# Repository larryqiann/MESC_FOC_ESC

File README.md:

# MESC_FOC_ESC
MESC, Molony ESC, STM32F303 based FOC+BLDC ready, HALL, Encoder, Sensorless, single sides, 2 layer, ~90A @48V

This ESC is intended as a cost optimised alternative to the VESC, by utilising:

Standalone, industry standard footprint gate drivers

Standard D2PAK or H2PAK FETs

Cheap (~2.5$) STM32F303CB microcontroller

Board dimensions 100mmx50mm, so that it can be panelised and manufactured by JLCPCB, or two boards can be combined into one 100mm2 JLCPCB

It is not cross compatible with VESC software, and does not intend to be. VESC has run away with itself in terms of cost, firmware abstraction... in the opinion of this project's author.

# Current Status:  

## Changes made by larryqiann:
Change power architecture to use MP9486A to create 12V rail, from  which 3.3V and 5V will be regulated to reduce quiescent power draw

Add CAN bus transceiver to support CAN bus integration because F303CB supports CAN2.0b

## Previous:

First build has been made. All functions... function.
Photos in folder! Video of prelim run to be added to Youtube.
Step down works
Step up for Gate drives works
Chip works, all inputs and outputs works
Some concerns about stability of internal opamps... Returning 1.5V instead of 1.6V. First chip soldered returned 1V, and fluctuated by +0.3/-0.1V. 
Motor spins in BLDC mode (6 step) with hall sensors, on Propdrive 2826 1200kV and with APS8072 50kV. Current run up to 20A phase, with minimal PCB heating with no heatsink. Only run to 23V so far, owing to PSU limitation.
FET switching time rather slow with 5 ohm resistors, limiting peak current to 2A (not counting FET and Gate drive resistance) will reduce to 2R7.

# Layout:  
Layout optimised to minimise current loop path, and keep the board completely single sided assembly.

For thermal management, the FETs have vias underneath the drains, which can be interfaced with a heatsink on the PCB underside, using silicone pad/thermal paste & insulator.

# MCU uses:
Timer1 on PA8,9,10 (high) and PB13,14,15 for PWM generation.

Onboard opamps for current sensing and paralelled comparators input on pins PA1,7, PB0.

Phase voltages can be measured on PA3,4,5, or alternatively, digitally read to detect ZC .

Main voltage can be read on PA0.

# Interfaces:
External Interfaces include Hall/Encoder, I2C, PWM in, UART, USB FS.

Hall sensors on Timer4 PB6,7,8, alternatively Encoder can be run on Tim4 PB6,7

Timer3 channel 1 for standard RC PWM input.

USART3 Tx Rx on PB10,11.
USB on PA11,12, with 1k5 pullup to signal FS mode. Canbe used for reflashing (hypothetically).

I2C1 on PA15(SCL) and PB9(SDA), with a plug for a standard SSD1306 breakout. Alternatively, inertial sensor board could be plugged on breakout wire.

Expected BoM cost:  
0.4USD board  
6x2USD FETs  
2.5USD MCU  
3x1USD gate drives  
1USD SMPS converter  
0.4USD inductor  
??? connector cost (dependent on what's fitted, wire in...)  
0.3USD linear reg  
~3USD caps (dependent on how many you want to solder on, which is dependent on distance to battery, desire to comply with EMC, headroom above FET voltage... etc.)  
0.6USD shunts and other resistors  
0.3USD Optional TVS diode, primarily to protect SMPS, which is only rated to 65V  
Total: ~23-24USD

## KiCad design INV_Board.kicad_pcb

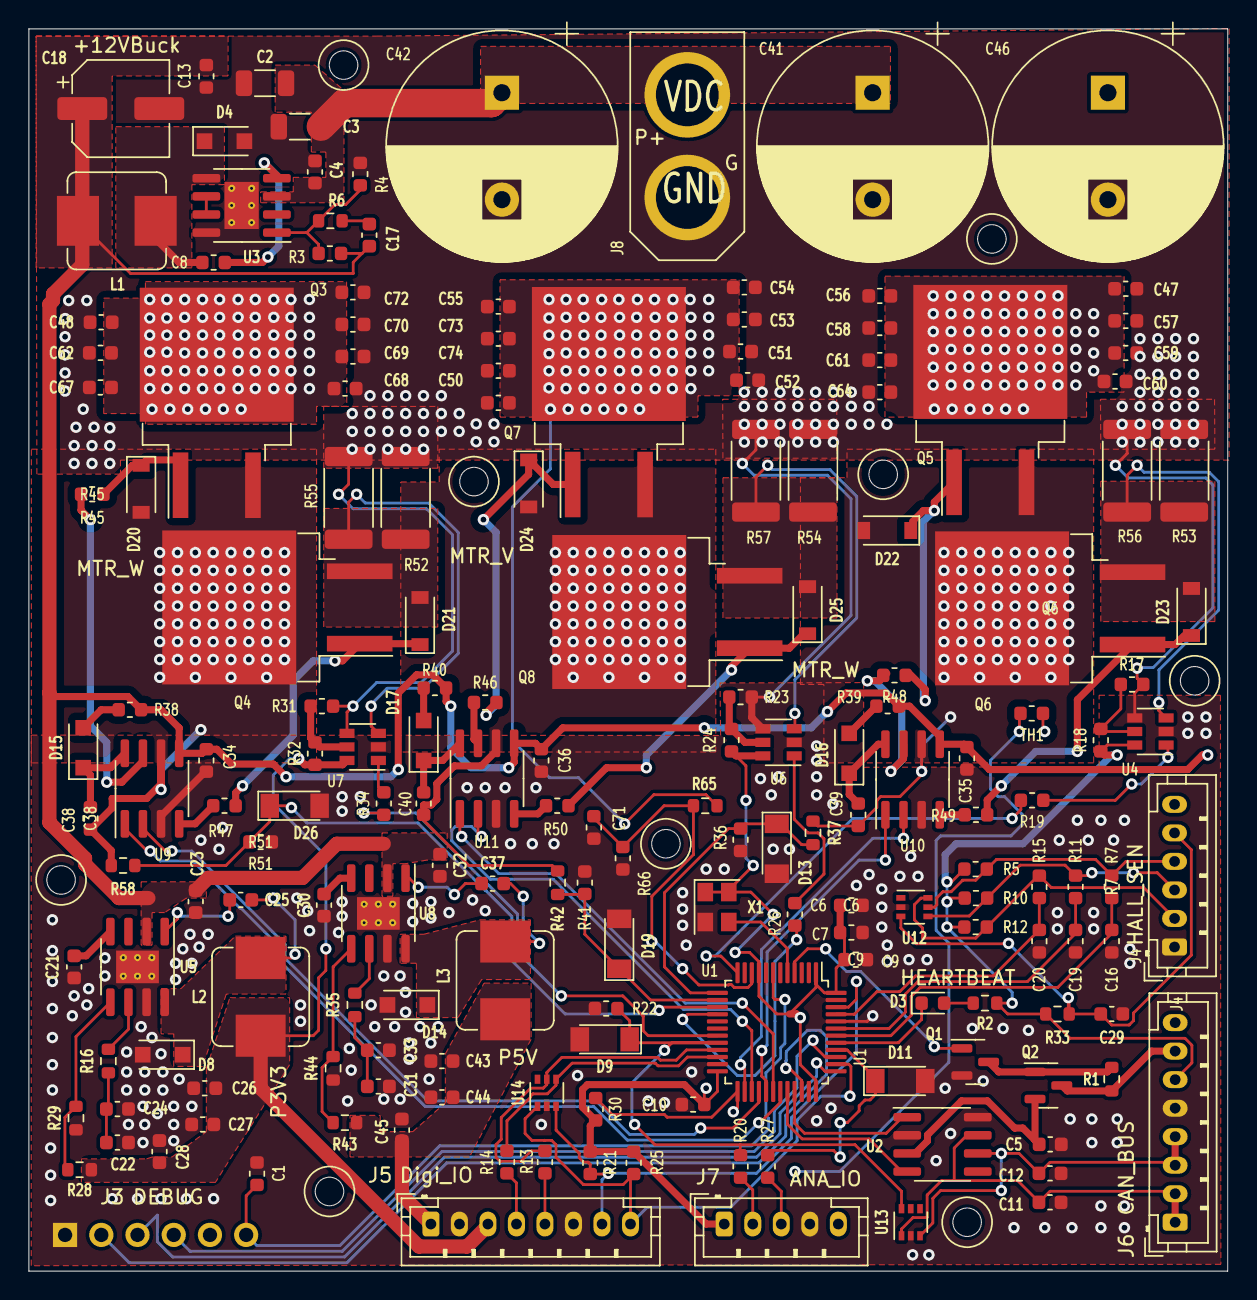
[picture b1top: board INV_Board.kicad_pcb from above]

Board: 4 copper layers, 84.1 x 87.1 mm, 177 parts (1 on the bottom side), 97 nets.

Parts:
C1, C4, C7, C9, C10, C17, C52, C68, C71: C_0.1uF_100V; C_0603_1608Metric
C2, C3: C_2.2uF 100V; C_1206_3216Metric
C5, C8, C25, C37: C_100nF_16V; C_0603_1608Metric
C6, C34, C35, C36, C38, C39, C40, C47, C48, C50, C51, C53, C54, C55, C56, C57, C58, C59, C60, C61, C62, C64, C67, C69, C70, C72, C73, C74: C_1uF_100V; C_0603_1608Metric
C11, C12: C_4.7nF; C_0603_1608Metric
C13, C23, C26, C27, C28, C32, C43, C44, C45: C_10uF_25V; C_0603_1608Metric
C16, C19, C20, C29: C_100pF_16V; C_0603_1608Metric
C18: C_100uF_25V; CP_Elec_6.3x7.7
C21, C30: C_8.2nF; C_0603_1608Metric
C22, C31: C_10pF; C_0603_1608Metric
C24, C33: C_5.1nF; C_0603_1608Metric
C41, C42, C46: CP_470uF+; CP_Radial_D16.0mm_P7.50mm
D3: LED_Small; LED_0603_1608Metric
D4, D8, D14, D15, D16, D17: D_Sch_100V_2A; D_SOD-123F
D9, D11, D13: D_Zener_3v3; D_MiniMELF
D19, D26: D_Zener_3V3; D_MiniMELF
D20, D21, D22, D23, D24, D25: D_Zener_16V; D_SOD-123
J3: Conn_01x06_Male; PinHeader_1x06_P2.54mm_Vertical
J4: Conn_01x06_Female; JST_PH_B6B-PH-K_1x06_P2.00mm_Vertical
J5, J6: Conn_01x08_Female; JST_PH_B8B-PH-K_1x08_P2.00mm_Vertical
J7: Conn_01x05_Male; JST_PH_B5B-PH-K_1x05_P2.00mm_Vertical
J8: Conn_01x02_Male; XT60
L1: L_47uH_2.0A; L_Bourns_SRP7028A_7.3x6.6mm
L2, L3: L_15uH_3A; L_Bourns_SRP7028A_7.3x6.6mm
Q1: 2N7002; SOT-23
Q2: AO3401A; SOT-23
Q3, Q4, Q5, Q6, Q7, Q8: CRSS037N10N; TO-263-2
R1, R37, R42, R58, R65: R_82k; R_0603_1608Metric
R2, R4, R6, R7, R11, R15, R30, R33: R_4k7; R_0603_1608Metric
R3: R_590K; R_0603_1608Metric
R5, R10, R12, R20, R21, R22, R25, R27, R36, R41, R51, R66: R_1.5k; R_0603_1608Metric
R13, R14: R_100; R_0603_1608Metric
R16, R35: R_5.76K; R_0603_1608Metric
R17, R18, R23, R24, R31, R32: R_30K; R_0603_1608Metric
R19, R26, R34: R_150; R_0603_1608Metric
R28, R43: R_10.2K; R_0603_1608Metric
R29: R_3.24K; R_0603_1608Metric
R38, R39, R40, R45, R46, R47, R48, R49, R50: R_5; R_0603_1608Metric
R44: R_1.96K; R_0603_1608Metric
R52, R53, R54, R55, R56, R57: Shunt; R_2512_6332Metric
TH1: Thermistor_NTC; R_0603_1608Metric
U1: STM32F303CBTx; LQFP-48_7x7mm_P0.5mm
U2: TJA1051T; SOIC-8_3.9x4.9mm_P1.27mm
U3: MP9486A; SOIC-8-1EP_3.9x4.9mm_P1.27mm_EP2.41x3.3mm_ThermalVias
U4, U6, U7: INA181; SOT-23-6
U5, U8: TPS54331DR; SOIC-8-1EP_3.9x4.9mm_P1.27mm_EP2.29x3mm_ThermalVias
U9, U10, U11: IR2181; SOIC-8_3.9x4.9mm_P1.27mm
U12, U13, U14: SMF05CT1G; SOT-363_SC-70-6
X1: ASE-xxxMHz; X1OSC

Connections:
#RES: C1.1, J3.6, U1.7 (NRST)
+3V3: C6.1, C7.1, C9.1, C10.1, C26.2, C27.2, C28.2, J5.3, J6.6, J7.1, L2.1, R2.1, R5.1, R10.1, R12.1, R18.1, R21.1, R24.1, R25.1, R28.1, R30.1, R32.1, R33.1, U1.1 (VBAT), U1.9 (VDDA), U1.24 (VDD), U1.36 (VDD), U1.48 (VDD), U4.6 (V+), U6.6 (V+), U7.6 (V+), X1.1 (EN), X1.4 (Vdd)
+5V: C43.2, C44.2, C45.2, J4.6, J5.1, J6.7, J7.5, L3.1, Q2.3 (D), R1.1, R43.1
+12V: C13.1, C17.1, C18.1, C23.1, C32.1, C34.1, C35.1, C36.1, J6.8, L1.2, R3.1, R38.1, R39.1, R40.1, U5.2 (VIN), U8.2 (VIN), U9.5 (VCC), U10.5 (VCC), U11.5 (VCC)
+VDC: C2.2, C3.2, C4.1, C41.1, C42.1, C46.1, C47.1, C48.1, C50.1, C51.1, C52.1, C53.1, C54.1, C55.1, C56.1, C57.1, C58.1, C59.1, C60.1, C61.1, C62.1, C64.1, C67.1, C68.1, C69.1, C70.1, C72.1, C73.1, C74.1, J8.2, Q3.2 (D), Q5.2 (D), Q7.2 (D), R65.1, U3.3 (VIN)
/Hall1: C16.1, R7.1, U1.42 (PB6)
/Hall2: C19.1, R11.1, U1.43 (PB7)
/Hall3: C20.1, R15.1, U1.45 (PB8)
/UGH: D22.1 (K), Q5.1 (G), R48.2
/UGL: D23.1 (K), Q6.1 (G), R49.2
/VGH: D24.1 (K), Q7.1 (G), R46.2
/VGL: D25.1 (K), Q8.1 (G), R50.2
/WGH: D20.1 (K), Q3.1 (G), R45.2
/WGL: D21.1 (K), Q4.1 (G), R47.2
/op1Vout: R19.1, U1.12 (PA2)
/op2Vout: R26.1, U1.16 (PA6)
/op3Vout: R34.1, U1.19 (PB1)
AnalogIn: D9.1 (K), R20.1, R22.1, U1.20 (PB2), U13.6 (K)
BoardTemp: R30.2, TH1.1, U1.25 (PB12)
CAN_EN: Q1.1 (G), U1.4 (PC15)
CAN_RXD: U1.32 (PA11), U2.4 (RXD)
CAN_TXD: U1.33 (PA12), U2.1 (TXD)
HeartBeat_LED: D3.1 (K), U1.41 (PB5)
I2CSCL: J5.8, R25.2, U1.38 (PA15), U14.1 (K)
I2CSDA: J5.7, R21.2, U1.46 (PB9), U14.3 (K)
ISU: D23.2 (A), Q6.3 (S), R53.1, R56.1, U4.3 (+)
ISV: D25.2 (A), Q8.3 (S), R54.1, R57.1, U6.3 (+)
ISW: D21.2 (A), Q4.3 (S), R52.1, R55.1, U7.3 (+)
Motor_T: C29.1, J4.5, R33.2, U12.3 (K)
unnamed: C5.1, Q2.2 (S), U2.3 (VCC)
unnamed: C8.1, U3.4 (BST)
unnamed: C8.2, D4.1 (K), L1.1, U3.5 (SW)
unnamed: C11.2, J6.1, J6.2, U2.7 (CANH), U13.1 (K)
unnamed: C12.2, J6.3, J6.4, U2.6 (CANL), U13.3 (K)
unnamed: C17.2, R6.2
unnamed: C21.1, U5.4 (SS)
unnamed: C22.1, C24.1, R16.2
unnamed: C25.1, U5.1 (BOOT)
unnamed: C25.2, D8.1 (K), L2.2, U5.8 (PH)
unnamed: C30.1, U8.4 (SS)
unnamed: C31.1, C33.1, R35.2
unnamed: C37.1, U8.1 (BOOT)
unnamed: C37.2, D14.1 (K), L3.2, U8.8 (PH)
unnamed: C38.1, D15.1 (K), U9.8 (VB)
unnamed: C39.1, D16.1 (K), U10.8 (VB)
unnamed: C40.1, D17.1 (K), U11.8 (VB)
unnamed: D3.2 (A), R2.2
unnamed: D15.2 (A), R38.2
unnamed: D16.2 (A), R39.2
unnamed: D17.2 (A), R40.2
unnamed: J4.2, R12.2, R15.2, U12.6 (K)
unnamed: J4.3, R10.2, R11.2, U12.4 (K)
unnamed: J4.4, R5.2, R7.2, U12.5 (K)
unnamed: J5.4, R14.1
unnamed: J5.5, R13.2
unnamed: J7.2, R20.2
unnamed: J7.3, R27.2
unnamed: Q1.3 (D), Q2.1 (G), R1.2
unnamed: R3.2, R4.1, R6.1, U3.1 (FB)
unnamed: R16.1, U5.6 (COMP)
unnamed: R17.1, R18.2, U4.5 (REF)
unnamed: R19.2, U4.1
unnamed: R23.1, R24.2, U6.5 (REF)
unnamed: R26.2, U6.1
unnamed: R28.2, R29.1, U5.5 (VSENSE)
unnamed: R31.1, R32.2, U7.5 (REF)
unnamed: R34.2, U7.1
unnamed: R35.1, U8.6 (COMP)
unnamed: R43.2, R44.1, U8.5 (VSENSE)
unnamed: R45.1, U9.7 (HO)
unnamed: R46.1, U11.7 (HO)
unnamed: R47.1, U9.4 (LO)
unnamed: R48.1, U10.7 (HO)
unnamed: R49.1, U10.4 (LO)
unnamed: R50.1, U11.4 (LO)
unnamed: U1.5 (PF0), X1.3 (OUT)
unnamed: U3.6 (DIM), U3.7 (EN)
PWMin: D11.1 (K), R27.1, U1.40 (PB4)
PhaseU: D13.1 (K), R36.1, R37.2, U1.13 (PA3)
PhaseV: D19.1 (K), R41.1, R42.2, U1.14 (PA4)
PhaseW: D26.1 (K), R51.1, R58.2, U1.15 (PA5)
SGU: C1.2, C2.1, C3.1, C4.2, C5.2, C6.2, C7.2, C9.2, C10.2, C11.1, C12.1, C13.2, C16.2, C18.2, C19.2, C20.2, C21.2, C22.2, C23.2, C24.2, C26.1, C27.1, C28.1, C29.2, C30.2, C31.2, C32.2, C33.2, C34.2, C35.2, C36.2, C41.2, C42.2, C43.1, C44.1, C45.1, C46.2, C47.2, C48.2, C50.2, C51.2, C52.2, C53.2, C54.2, C55.2, C56.2, C57.2, C58.2, C59.2, C60.2, C61.2, C62.2, C64.2, C67.2, C68.2, C69.2, C70.2, C71.2, C72.2, C73.2, C74.2, D4.2 (A), D8.2 (A), D9.2 (A), D11.2 (A), D13.2 (A), D14.2 (A), D19.2 (A), D26.2 (A), J3.1, J4.1, J5.2, J5.6, J6.5, J7.4, J8.1, Q1.2 (S), R4.2, R17.2, R22.2, R23.2, R29.2, R31.2, R36.2, R41.2, R44.2, R51.2, R52.2, R53.2, R54.2, R55.2, R56.2, R57.2, R66.2, TH1.2, U1.8 (VSSA), U1.23 (VSS), U1.35 (VSS), U1.44 (BOOT0), U1.47 (VSS), U2.2 (GND), U2.8 (S), U3.8 (GND), U3.9 (EP), U4.2 (GND), U4.4 (-), U5.7 (GND), U5.9 (EP), U6.2 (GND), U6.4 (-), U7.2 (GND), U7.4 (-), U8.7 (GND), U8.9 (EP), U9.3 (COM), U10.3 (COM), U11.3 (COM), U12.2 (A), U13.2 (A), U14.2 (A), X1.2 (GND)
STRx: R14.2, U1.22 (PB11), U14.4 (K)
STTx: R13.1, U1.21 (PB10), U14.5 (K)
SWCLK: J3.3, U1.37 (PA14)
SWDIO: J3.2, U1.34 (PA13)
SWO: J3.4, U1.39 (PB3)
SWU: C39.2, D22.2 (A), Q5.3 (S), Q6.2 (D), R37.1, U10.6 (VS)
SWV: C40.2, D24.2 (A), Q7.3 (S), Q8.2 (D), R42.1, U11.6 (VS)
SWW: C38.2, D20.2 (A), Q3.3 (S), Q4.2 (D), R58.1, U9.6 (VS)
UHin: U1.29 (PA8), U10.1 (HIN)
ULin: U1.26 (PB13), U10.2 (LIN)
VHin: U1.30 (PA9), U11.1 (HIN)
VLin: U1.27 (PB14), U11.2 (LIN)
Vsense_MCU: C71.1, R65.2, R66.1, U1.10 (PA0)
WHin: U1.31 (PA10), U9.1 (HIN)
WLin: U1.28 (PB15), U9.2 (LIN)

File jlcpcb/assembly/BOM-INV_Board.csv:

Comment,Designator,Footprint,LCSC
AO3401A,Q2,SOT-23, C15127
C_10pF,"C22,C31",C_0603_1608Metric, C1634
C_5.1nF,"C24,C33",C_0603_1608Metric, C53987
STM32F303CBTx,U1,LQFP-48_7x7mm_P0.5mm,C108516
D_Zener_3v3,"D11,D13,D9",D_MiniMELF,C145245
C_100nF_16V,"C25,C37,C5,C8",C_0603_1608Metric,C14663
C_100pF_16V,"C16,C19,C20,C29",C_0603_1608Metric,C14858
L_47uH_2.0A,L1,L_Bourns_SRP7028A_7.3x6.6mm,C149588
D_Sch_100V_2A,"D14,D4,D8",D_SOD-123F,C14996
R_82k,"R1,R37,R42,R58,R65",R_0603_1608Metric,C17840
L_15uH_3A,"L2,L3",L_Bourns_SRP7028A_7.3x6.6mm,C182182
INA181,"U4,U6,U7",SOT-23-6,C2058943
R_100,"R13,R14",R_0603_1608Metric,C22775
R_150,"R19,R26,R34",R_0603_1608Metric,C22808
R_1.5k,"R10,R12,R20,R21,R22,R25,R27,R36,R41,R5,R51,R66",R_0603_1608Metric,C22843
LED_Small,D3,LED_0603_1608Metric,C2286
R_1.96K,R44,R_0603_1608Metric,C22975
R_3.24K,R29,R_0603_1608Metric,C22978 
R_30K,"R17,R18,R23,R24,R31,R32",R_0603_1608Metric,C22984
R_4k7,"R11,R15,R2,R30,R33,R4,R6,R7",R_0603_1608Metric,C23162
R_5,"R38,R39,R40,R45,R46,R47,R48,R49,R50",R_0603_1608Metric,C23164
R_5.76K,"R16,R35",R_0603_1608Metric,C23189
R_590K,R3,R_0603_1608Metric,C23203
R_10.2K,"R28,R43",R_0603_1608Metric,C25804
Shunt,"R52,R53,R54,R55,R56,R57",R_2512_6332Metric,C270947
D_Zener_16V,"D20,D21,D22,D23,D24,D25",D_SOD-123,C27754 
C_8.2nF,"C21,C30",C_0603_1608Metric,C27920
C_0.1uF_100V,"C1,C10,C17,C4,C52,C68,C7,C71,C9",C_0603_1608Metric,C28233
IR2181,"U10,U11,U9",SOIC-8_3.9x4.9mm_P1.27mm,C380794
CRSS037N10N,"Q3,Q4,Q5,Q6,Q7,Q8",TO-263-2,C455308
C_4.7nF,"C11,C12",C_0603_1608Metric,C53987
D_Sch_100V_2A,"D15,D16,D17",D_SOD-123F,C64898
C_2.2uF 100V,"C2,C3",C_1206_3216Metric,C650969
ASE-xxxMHz,X1,X1OSC,C70556
C_100uF_25V,C18,CP_Elec_6.3x7.7,C72477
D_Zener_3V3,"D19,D26",D_MiniMELF,C8056
2N7002,Q1,SOT-23,C8545
C_1uF_100V,"C34,C35,C36,C38,C39,C40,C47,C48,C50,C51,C53,C54,C55,C56,C57,C58,C59,C6,C60,C61,C62,C64,C67,C69,C70,C72,C73,C74",C_0603_1608Metric,C91151
Thermistor_NTC,TH1,R_0603_1608Metric,C92367
C_10uF_25V,"C13,C23,C26,C27,C28,C32,C43,C44,C45",C_0603_1608Metric,C96446 
TPS54331DR,"U5,U8",SOIC-8-1EP_3.9x4.9mm_P1.27mm_EP2.29x3mm_ThermalVias,C9865 
Conn_01x08_Female,J6,JST_PH_B8B-PH-K_1x08_P2.00mm_Vertical,
SMF05CT1G,U14,SOT-363_SC-70-6,
MP9486A,U3,SOIC-8-1EP_3.9x4.9mm_P1.27mm_EP2.41x3.3mm_ThermalVias,
TJA1051T,U2,SOIC-8_3.9x4.9mm_P1.27mm,
SMF05CT1G,U12,SOT-363_SC-70-6,
SMF05CT1G,U13,SOT-363_SC-70-6,
Conn_01x08_Female,J5,JST_PH_B8B-PH-K_1x08_P2.00mm_Vertical,
CP_470uF+,C46,CP_Radial_D16.0mm_P7.50mm,
Conn_01x02_Male,J8,XT60,
Conn_01x06_Male,J3,PinHeader_1x06_P2.54mm_Vertical,
Conn_01x06_Female,J4,JST_PH_B6B-PH-K_1x06_P2.00mm_Vertical,
CP_470uF+,C42,CP_Radial_D16.0mm_P7.50mm,
CP_470uF+,C41,CP_Radial_D16.0mm_P7.50mm,
Conn_01x05_Male,J7,JST_PH_B5B-PH-K_1x05_P2.00mm_Vertical,

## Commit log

2022-05-13 Edit README
2022-05-13 Schematic Changes (Incomplete)
2022-05-14 Checkpoint before deleting MCU ISense
2022-05-15 Save progress
2022-05-16 Update progress
2022-05-19 00A revision as ordered
    00A version of board has been ordered for assembly. Warning: this commit contains some fixes which were not part of the order
